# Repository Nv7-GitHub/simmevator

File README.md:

# simmevator

An elevator tracker and floor display for Simmons Hall, MIT.

A barometer rides in each elevator car and works out which floor the car is on. It
broadcasts that over LoRa to a bridge in its own shaft, which relays it over
ESP-NOW to a screen on every landing of that shaft. Each screen shows the floor in
numbers you can read from down the corridor, an up/down arrow while the car is
moving, the transmitter's battery voltage, and how far that elevator has travelled
in the last day.

Three shafts are covered: A, B and C. A and C serve a basement as well as floors
1-10, so they have eleven landings each; B has ten. That is 3 transmitters, 3
bridges and 32 displays.

| | elevator A | elevator B | elevator C |
|---|---|---|---|
| landings | B, 1-10 | 1-10 | B, 1-10 |
| displays | 11 | 10 | 11 |
| LoRa frequency | 913.0 MHz | 915.0 MHz | 917.0 MHz |
| ESP-NOW channel | 6 | 1 | 11 |
| `txId` | `'A'` | `'B'` | `'C'` |

The three systems are independent end to end. A car is heard only by its own
bridge, a screen only ever sees its own shaft's car, and no packet crosses from one
shaft to another.

Each car node runs on a battery, unattended, for about seven weeks.

---

## How it works

### The hard part is not what you would guess

A floor is about 2.9 m of altitude, and a BMP390 resolves that easily — noise in
this shaft is 0.045 m, sixty times smaller. The difficulty is that **the reference
pressure moves.** Over a 3 h capture in this building the sea-level reference
wandered 9.9 m of apparent altitude, more than three floor heights. Any fixed
pressure-to-floor table slides through several floors in an evening.

So absolute altitude cannot decide the floor. Two facts rescue it:

- **A trip is short** — 5 to 60 seconds, over which the weather moves the
  reference by less than 0.05 m. The *change* in altitude across a trip is clean
  even when the absolute value is not.
- **Floors are a lattice.** Every jump between stops is an integer multiple of the
  floor pitch, so `round(jump / pitch)` is a strong error-correcting code.

The algorithm therefore reads floor *changes* from jumps between stops and treats
absolute position as a slowly-tracked side quantity. It learns the building as it
goes — the floor spacing, each landing's height, how many floors exist — with
nothing configured in advance. On the reference capture it converges in five
minutes to a pitch of 2.871 m and ten floors, and stays within ±1%.

The algorithm is not this repo's invention. It was developed and measured against
real data in the [`elevatormons`](../elevatormons) bring-up repo, and is fully
documented in `elevatormons/docs/ALGORITHM.md` — including the four approaches
that were tried and failed, which are more instructive than the one that worked.
This repo ports it to C++ and builds a system around it.

### Why the decision happens in the car

The node holds the sensor, so it sees an unbroken 1 Hz stream and decides the
floor locally. It broadcasts the answer, not the raw pressure.

That one choice makes radio loss harmless. A dropped packet can only *age* what a
screen shows; it can never corrupt the floor, because the next packet carries the
current floor outright. There is no state to resync and no way for a bad link to
produce a wrong number. If the bridge decided the floor instead, every dropout
would become a correctness problem.

### The three devices

```
  ELEVATOR CAR (battery)          MID-SHAFT (wall)          EVERY LANDING (wall)
  ┌──────────────────────┐        ┌──────────────┐          ┌──────────────┐
  │ XIAO ESP32S3         │        │ XIAO ESP32S3 │  ESP-NOW │ CYD x10/x11  │
  │  BMP390 @ 4 Hz       │  LoRa  │ + Wio-SX1262 │ ───────► │ ILI9341      │
  │  FloorMonitor @ 1 Hz │ ─────► │              │  flood   │ relay + draw │
  │  model in NVS        │913/915/│ LoRa -> mesh │ ch 6/1/11│              │
  │  battery sense       │917 MHz │ origin node  │ ◄──────► │ peer relay   │
  │  Wio-SX1262          │        └──────────────┘          └──────────────┘
  └──────────────────────┘
```

One of these per shaft, three times over. The column of radio settings is the only
difference between them.

**The transmitter** samples the barometer, runs the floor algorithm, and sends two
kinds of packet: an 8-byte `STATE` every 2 seconds while the car is moving, and a
24-byte `STATS` every 60 seconds carrying battery voltage, distance travelled, and
the learned building model.

**The bridge** does nothing but listen on LoRa and re-emit over ESP-NOW. It holds
no state worth losing.

**The displays** flood packets to each other so the signal reaches floors the
bridge cannot: every screen rebroadcasts each new sequence number exactly once, up
to eight hops. Flooding rather than a fixed 5→6→7 chain means one unplugged screen
does not cut off everything above it.

### Why the three systems do not interfere

**Separate LoRa frequencies, because three cars on one frequency is pure ALOHA.**
There is no carrier sense: a transmitter that is about to send has no idea another
shaft's car is mid-packet. A STATE packet is 297 ms and goes out every 2 s while
the car is active. STATE is not gated on motion alone - it keeps running for 10 s
past every stop - so the duty fraction is the 0.90 STATE-active figure, and each
car offers `0.5 x 0.90 = 0.45` packets per second. ALOHA's vulnerable window is
two packet lengths, `2 x 0.297 = 0.594 s`, so a given packet survives two
interferers with probability `exp(-2 x 0.45 x 0.594) = 0.586` - about two STATE
packets in five lost, on top of the 5.21% the shaft already costs
(`ALGORITHM.md` §9), and concentrated in exactly the evening peak when all three
cars are busy at once. So A, B and C sit on 913.0, 915.0 and 917.0 MHz: 2 MHz of
separation against a 125 kHz occupied bandwidth, sized for a transmitter passing
close to another shaft's bridge rather than for the typical case. A per-elevator
sync word would *not* fix this and must not be mistaken for a fix - it is checked
after demodulation, so it classifies wreckage rather than preventing it.
`docs/PROTOCOL.md` carries the full arithmetic.

**Separate ESP-NOW channels, because each mesh should stay the system that was
measured.** No display ever needs another shaft's data, so the three floods run on
channels 6, 1 and 11 and each one remains the ten- or eleven-node, single-origin
flood that `docs/MESH.md` measured and tuned - so every number in it stays valid as
written. One building-wide flood instead would break
in two ways: the per-bridge `origSeq` counters would collide, because the dedup ring
tests sequence numbers for equality with no notion of who minted them, so bridge
A's frame 4113 would silently swallow bridge C's; and the 5-40 ms relay jitter
window would be swamped, since 32 displays and 3 bridges put roughly 96
transmissions of about 1.3 ms each into a 35 ms window, some 3.5x oversubscribed,
re-creating the exact collision the jitter exists to prevent. Channel isolation
makes both problems not exist rather than patching them; the only thing given up is
cross-shaft path diversity, which is worthless when the shafts are far apart.
`docs/MESH.md` works through both.

### Why the update rate is what it is

Airtime is the entire power budget. A LoRa packet at SF10 costs hundreds of
milliseconds at about 118 mA, and the car in this building is *moving* 71% of an
evening peak. Thirty days off a 10 Ah LiFePO4 pack means staying under 40 mA
average. Send a 297 ms packet every 2 s around the clock and the radio alone is
~21 mA; stay awake between samples and the baseline is ~25 mA instead of ~3 mA.
Together that is ~47 mA - the requirement is missed before anything else has
gone wrong.

Two changes fix it without making the display feel slower:

- **Transmit only while the car is moving.** Nothing changes while it is parked,
  so there is nothing to say. A 60-second heartbeat carries the slow statistics
  and proves the transmitter is alive.
- **Detect motion at 4 Hz, run the algorithm at 1 Hz.** The stillness test gets
  fast samples so motion onset is caught within 250 ms and the first packet
  fires immediately; the algorithm itself still sees the 1 Hz stream its
  constants were tuned for. Between samples the chip light-sleeps, which is the
  difference between a 3 mA baseline and a 25 mA one.

That lands at roughly **23 mA average, about 50 days** on a 10 Ah LiFePO4 pack,
using the evening-peak traffic rate — a real week including nights does better.

That is arithmetic, not a measurement. No board has been on a meter yet, and the
light-sleep floor is the number in it I would trust least: the ~3 mA is the
datasheet figure, while the actual XIAO board also carries a power LED and a
charge IC. The spec lists the four unmeasured draws and what to do about them.

### One correction to the radio settings

`elevatormons/platformio.ini` configures the barometer link at **BW62.5 kHz**, but
`ALGORITHM.md §9` records that the actual field run — the one that measured 5.21%
packet loss over three hours in this shaft — was at **BW125 kHz and only 14 dBm**.

This project uses BW125 at 22 dBm on all three shafts. The 915.0 MHz that the
bring-up repo and the field run used is now elevator B's frequency specifically -
A and C sit 2 MHz either side of it, and nothing else about the link differs
between them. That is the configuration with real in-shaft
evidence, running with 8 dB more margin than the run that produced the 5.21%
figure, and it costs 297 ms per packet instead of 725 ms. The same section notes
that loss barely tracks signal-to-noise (r = −0.13) — it is shadowing and
interference, not a decode floor — so buying margin with a higher spreading factor
would cost airtime linearly and buy very little.

---

## What each screen shows

```
┌────────────────────────────┬──────────────┐
│                            │      ▲       │
│      ██████     ██         │    UP        │
│      ██  ██     ██         │              │
│      ██  ██     ██         │  12.7 V      │
│      ██  ██     ██         │  ■■■■■□      │
│      ██████     ██         │              │
│                            │  2.1 mi      │
│                            │  today       │
└────────────────────────────┴──────────────┘
```

The floor number is drawn as vector segments rather than a font — anything large
enough to read at distance looks soft as a bitmap. While the car is moving the
number sweeps through the intermediate floors and the arrow lights up; on arrival
it snaps to the floor the algorithm confirmed.

Battery voltage and the 24-hour distance come from the transmitter once a minute,
so every screen in that shaft agrees. Between heartbeats each screen extrapolates
the distance from floor changes it observes, so the number ticks in real time
rather than jumping once a minute.

If a screen stops hearing the mesh it dims, then greys out and turns its onboard
LED amber — a dead link is visible from the corridor rather than silently showing
a floor from twenty minutes ago.

That is normal operation. There are three further states that appear only while a
shaft is being commissioned or is misconfigured, all derived from fields the wire
already carries: **LEARNING**, showing how many landings the car has spanned so far
over the word `LEARNING` and `OF 11`; **ANCHORING**, asking for a ride to both ends of the shaft
after the transmitter restored its model from NVS; and **CHECK SHAFT**, which means
the car is confidently reporting a floor count this shaft does not have. The last
one is the whole reason the others exist. An elevator A car commissioned over a
period in which nobody presses B learns a span of ten landings, is internally
consistent, sets its model ready, and would label every screen in the shaft one
floor too low indefinitely - and it is the display, holding the only copy of how
many landings the building has, that can catch it. That mismatch is CHECK SHAFT's
only cause, and because every display in a shaft carries the same label table and
hears the same bridge, it appears on all of them at once or on none. It does not
catch a mis-flashed display: the mesh channels are 6, 1 and 11, which do not
overlap, so a display flashed for the wrong shaft never hears its landing's bridge
at all and sits on the splash screen forever. `docs/FLASHING.md` has the
commissioning procedure. `--` means "this screen has heard frames but has no
confirmed floor"; a screen that has heard nothing since boot still shows the
splash.

---

## Documentation

| Document | What is in it |
|---|---|
| [Design spec](docs/superpowers/specs/2026-09-11-simmevator-design.md) | The whole system: power budget, protocols, verification gates, parts list |
| [Three-elevator deployment](docs/superpowers/specs/2026-09-18-three-elevator-deployment-design.md) | The per-shaft frequency and channel plan, the basement, the commissioning screens |
| [docs/HARDWARE.md](docs/HARDWARE.md) | Wiring, the battery divider, the buck regulator, antenna placement |
| [docs/FLASHING.md](docs/FLASHING.md) | Which firmware goes on which board, and how |
| [docs/PROTOCOL.md](docs/PROTOCOL.md) | Both wire formats, field by field |
| [docs/MESH.md](docs/MESH.md) | How the ESP-NOW flood behaves and how to debug it |
| [docs/ALGORITHM_PORT.md](docs/ALGORITHM_PORT.md) | How the C++ port maps to the Python reference, and the evidence it matches |
| `elevatormons/docs/ALGORITHM.md` | The algorithm itself — the source of truth, not maintained here |

---

## Building

PlatformIO. Nine firmware environments - three roles across three elevators:

```bash
pio run -e elevator_tx_b   -t upload    # shaft B's car node
pio run -e bridge_rx_b     -t upload    # shaft B's bridge
pio run -e floor_display_b -t upload    # each of shaft B's screens
pio test -e native                      # host unit tests
```

Substitute `_a` or `_c` for the other two shafts. The suffix is the whole of an
image's identity: it carries the LoRa frequency, the ESP-NOW channel, the `txId`
and the floor label table, so a display built `_b` and hung in shaft A is deaf on
channel 1 while that landing's bridge floods channel 6, and never leaves its splash
screen. There is no runtime elevator selection to correct it with.
`docs/FLASHING.md` has the which-image-on-which-board table, the board labelling,
and the commissioning check that catches exactly that mistake.

The port is verified by replaying the real 3 h capture through the actual C++
implementation and diffing it against the Python reference sample by sample:

```bash
pio run -e sim && .pio/build/sim/program sim/cpp_broadcasts.csv
python3 sim/compare_to_python.py sim/cpp_broadcasts.csv
```

The gate that matters is the first line of the comparator's output: the C++
floor sequence has to be identical to the Python's over all 10,950 samples. Five
numeric gates bound the rest - ten floors, 2.871 m pitch ±1 mm, 3409 m travelled
±0.1%, 357 floor-to-floor moves ±1, 255 confirmed stops ±1.

`ALGORITHM.md` §5 reports 356 moves and 256 stops, and that is not a
disagreement: §5 measured the raw capture, which is a radio log with 49 dropouts
in it, while the replay runs the gap-filled 1 Hz stream the node would actually
have been handed. The Python reference produces 357/255 on that input too.
`docs/ALGORITHM_PORT.md` §6 works through it.

---

## What this will not do

- **There is no absolute anchor.** The floor index is integrated from jumps, so a
  rounding that goes wrong stays wrong until the car happens to correct it. An
  absolute readout from a tracked datum was tried and is measurably worse.
- **It is safe to about 3 hPa/h of pressure change** with the floor count still
  exact, and degrades rather than diverges past that. A typical weather front is
  1–2 hPa/h; the fastest rate in the reference capture was 0.88 hPa/h.
- **Turbulence headroom is roughly 1.5–2×** a confirmed gusty evening. Not zero,
  not large.
- **The constants are tuned to this building and this sensor.** They are measured,
  not universal.
- **Battery voltage is ±2–3% before calibration**, about ±0.4 V at 12 V. Enough to
  answer "does this need charging?", not a fuel gauge.
- **The 24-hour window is relative to uptime**, not wall-clock — there is no RTC.
  After a reboot it reports less than a day of history and says so.
- **A screen shows one car.** A landing served by all three shafts needs three
  screens, one per shaft. There is no "which car arrives first" logic anywhere in
  the system, and there cannot be without building one: each display is on its own
  shaft's mesh channel and physically never hears the other two cars.

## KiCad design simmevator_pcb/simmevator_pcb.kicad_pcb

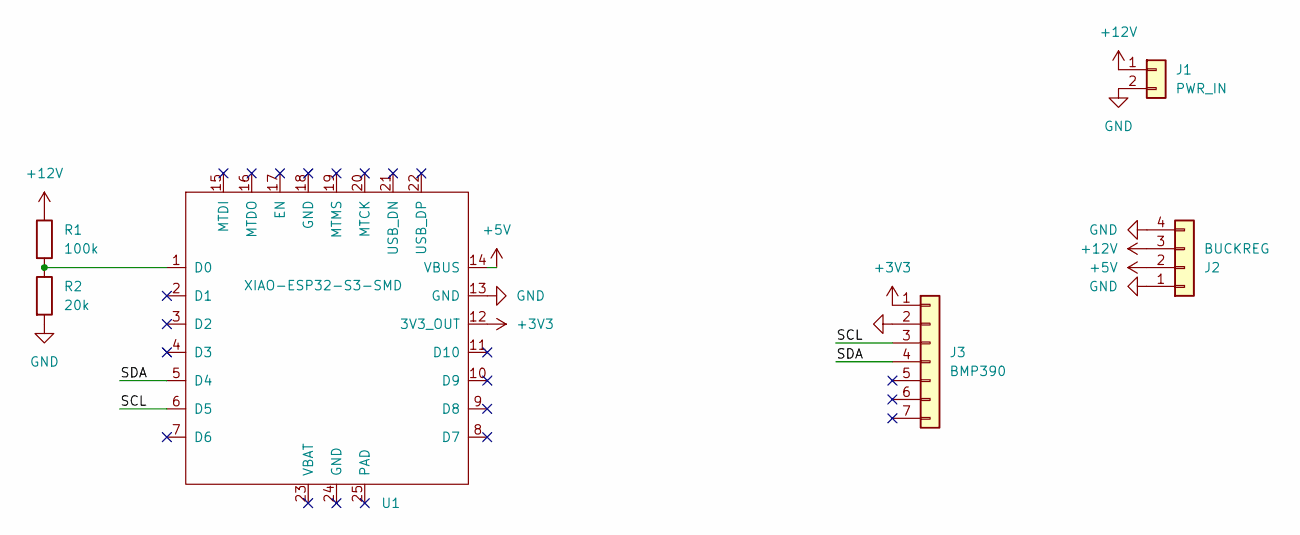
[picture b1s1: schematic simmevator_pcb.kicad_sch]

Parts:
J1: PWR_IN; SolderWire-1.5sqmm_1x02_P6mm_D1.7mm_OD3mm_Relief
J2: BUCKREG
J3: BMP390; PinHeader_1x07_P2.54mm_Vertical
R1: 100k; R_Axial_DIN0207_L6.3mm_D2.5mm_P10.16mm_Horizontal
R2: 20k; R_Axial_DIN0207_L6.3mm_D2.5mm_P10.16mm_Horizontal
U1: XIAO-ESP32-S3-SMD; XIAO-ESP32-S3-DIP

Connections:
+3V3: J3.1, U1.12 (3V3_OUT)
+5V: J2.2, U1.14 (VBUS)
+12V: J1.1, J2.3, R1.1
/SCL: J3.3, U1.6 (D5)
/SDA: J3.4, U1.5 (D4)
GND: J1.2, J2.1, J2.4, J3.2, R2.2, U1.13 (GND)
unnamed: R1.2, R2.1, U1.1 (D0)

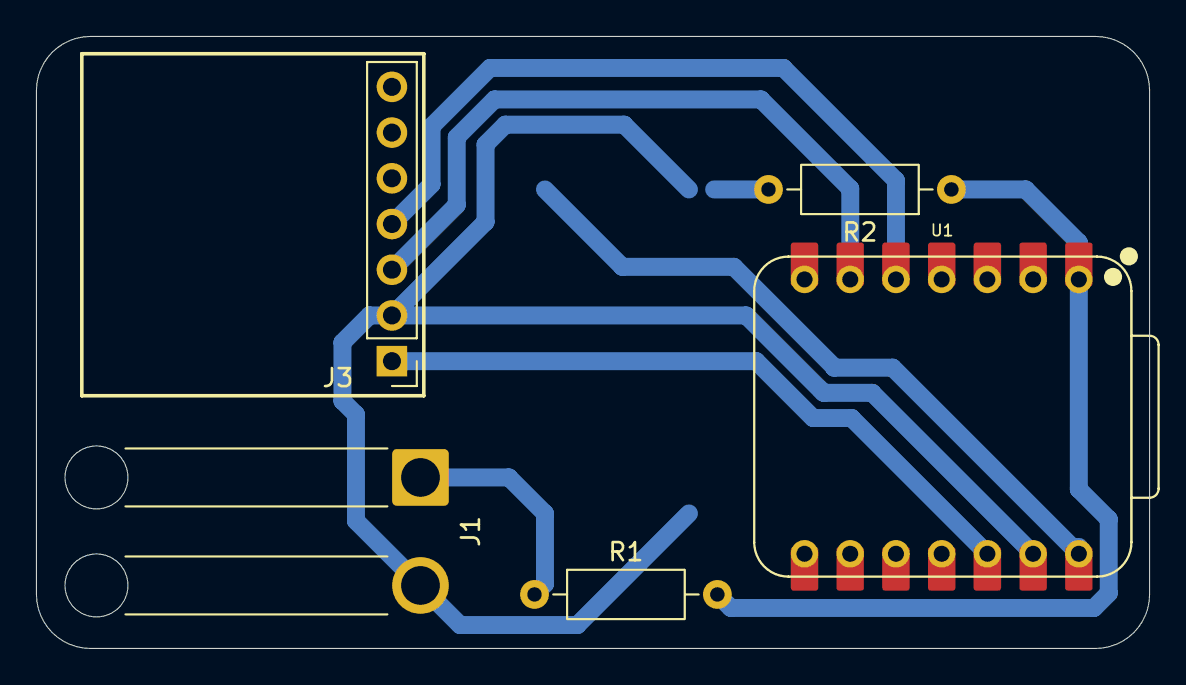
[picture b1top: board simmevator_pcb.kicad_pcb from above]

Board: 2 copper layers, 61.8 x 34.0 mm, 6 parts (1 on the bottom side), 7 nets.
